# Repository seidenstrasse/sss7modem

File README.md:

SSS7 Modems
===========
SSS7 is the **S**eidenstrasse **S**ignaling **S**ystem 7.

**This is still work in progress, contact me before building hardware !**

This repository contains the schematics its the hardware,
along with a description of the physical layer and the transport layer.
The actual application layer is developed independently of this project.

Physical Layer
--------------
The physical layer is based on a RS485-like two wire bus
(normal RS485 has different levels when idle),
using the *MCP2551* is used as transceiver chip.
Since this chip is actually a CAN-transceiver,
it has a well defined behaviour in case of collisions
and it allows to read back the bits which were actually on the bus while sending.
For regular RS485 transceivers a collision on the bus results
in one transceiver pulling the bus while the other one pulls it high,
effectively creating a temporary short circuit.
Therefore using a CAN-transceiver is preferable for our bus configuration.

The MCP2551 requires that the levels of the differential data lines are within +-7V
of its ground potential.
This a bit of a problem, since it is not really practical to run an additional wire
along the bus to provide a common ground.
Additionally routers may use power supplies which do not have a floating ground potential
(e.g. a computer power supply).
Connecting the ground rails of two non-floating power supplies will lead to a problems.
Therefore an isolated DC/DC converter is used to provide a floating supply voltage
for the transceiver chip and the data lines are isolated using optocouplers.
Still a common ground potential for all nodes is required for the transceiver chips to work.
This is solved by adding diodes in blocking direction between the floating 5v rail and both data lines
and between the chips ground and both data lines.
If the potential of the high data line is more than 0.7v above the floating 5v rail,
on of diodes will become conducting effectively shifting the floating grounds potential up.
Likewise if the potential of the low data line is more than 0.7v below the floating ground rail,
the ground rail will be shifted down.
Hence the floating grounds rails of all modems connected to bus will be within +-0.7v
relative to each other(not considering the voltage drop over the long wires).

Additionally these diodes suppress voltages spikes on the bus,
protecting the transceiver.

Using a sss7modem any device with a decent UART (microcontroller, raspi ...)
can communicate over long distances (1000m+).
The data is send at 9600 Baud (aka. 9,6kbit/s) with a maximum baudrate error of +-5%,
to ensure that even the slowest microcontroller can participate in the communication.
A slow bitrate also necessary to keep communication and collision detection reliable over longer
distances and allows to use slower (and cheaper) optocouplers.

Transport Layer
---------------

### Frame format:
``` 0xAA 0xFE <payload 16 bytes> <payload crc 1byte> ```

19 bytes total

**Header: 0xAA 0xFE**
- Choosen emperically to help the Uarts to synchronize
- Improves detection of two headers colliding

**CRC-Type: Maxim iButton 8-bit**
Polynomial: x^8 + x^5 + x^4 + 1 (0x8C)
Initial value: 0x0

### Communication Protocol

- **Not final, use with caution**
- Frames are sent using standard RS232 Uarts connected to sss7 modems
- Uarts should be configured to: 9600baud, 8bits, 1 stop bit, no flow-control, no parity
- Every node can send a frame at an arbitrary point in time,
    unless it is currently receiving a frame.
- Collision detection on the sender side is done by reading back each sent byte.
- Collision checking on receiver side, is done by checking the CRC and frame header.
- If a frame has been started and there are no new bytes received for 50ms,
    the frame is considered timed out and all received data can be dropped.
- Incoming messages are stored in a fifo until the application retrieves them.
- The receive fifo has a size of at least 2 messages.
- If the fifo is full all new messages will be dropped until messages are retrieved from the fifo.
    It is up to the application to retrieve message in time.
- Even if sending was successful, there is still a chance that the receiver could not
    receive the frame due to missing buffer space or not enough processing time to react.
    **Important messages should utilize a ack-mechanism.**
- It is up to the application to resend messages in case of a collision/missing ack.

### Planned API
- **Not final, use with caution**
- All calls are non-blocking,
    any real work should be done by ISRs or an eventloop, which is called periodically.

- **sss7_can_send()**

    Checks wether we see the bus as idle.
    Return true iff. we neither are currently receiving a frame
    nor are sending a frame of our own.

- **sss7_send_failed()**

    Checks the send error flag.
    Returns true if the last attempt at sending a frame failed.
    An attempt is considered failed if the Uart reads back a different byte than the byte send out.
    This indicates either a collision or a hardware failure.

- **sss7_send(payload)**

    Constructs a frame around the payload and prepares for sending.
    The actual sending is either done in the ISR or by the eventloop, depending on the platform.
    The frame is completely sent iff. ```sss7_can_send() && !sss7_send_failed()``` holds.

- **sss7_has_received()**

    Returns True iff. the receive fifo contains at least one message.

- **sss7_get_received(payload)**

    Retrieves the oldest message from the receive fifo.
    It is up the application to provide sufficient space in payload.
    Does nothing sss7_has_received() is false.

Licenses
--------

Anything in the folder hardware/libs/smisitoto_eu/ is taken from http://smisioto.no-ip.org/elettronica/kicad/kicad-en.htm
The files are made avaible under the Creative Commons license rev2.5 Attribution-ShareAlike. (see https://creativecommons.org/licenses/by-sa/2.5/)

The Chaos InKL logo is licensed CC BY-NC-SA 3.0.

The seidenstrasse logo and my personal logo are not available under an open license.
Therefore you should ask for permission before using the seidenstrasse logo in derived works.
Also please remove my personal logo if I am not involved in your project.

The schematics and pcb layout files in hardware are released under the *CERN Open Hardware License v1.2*.

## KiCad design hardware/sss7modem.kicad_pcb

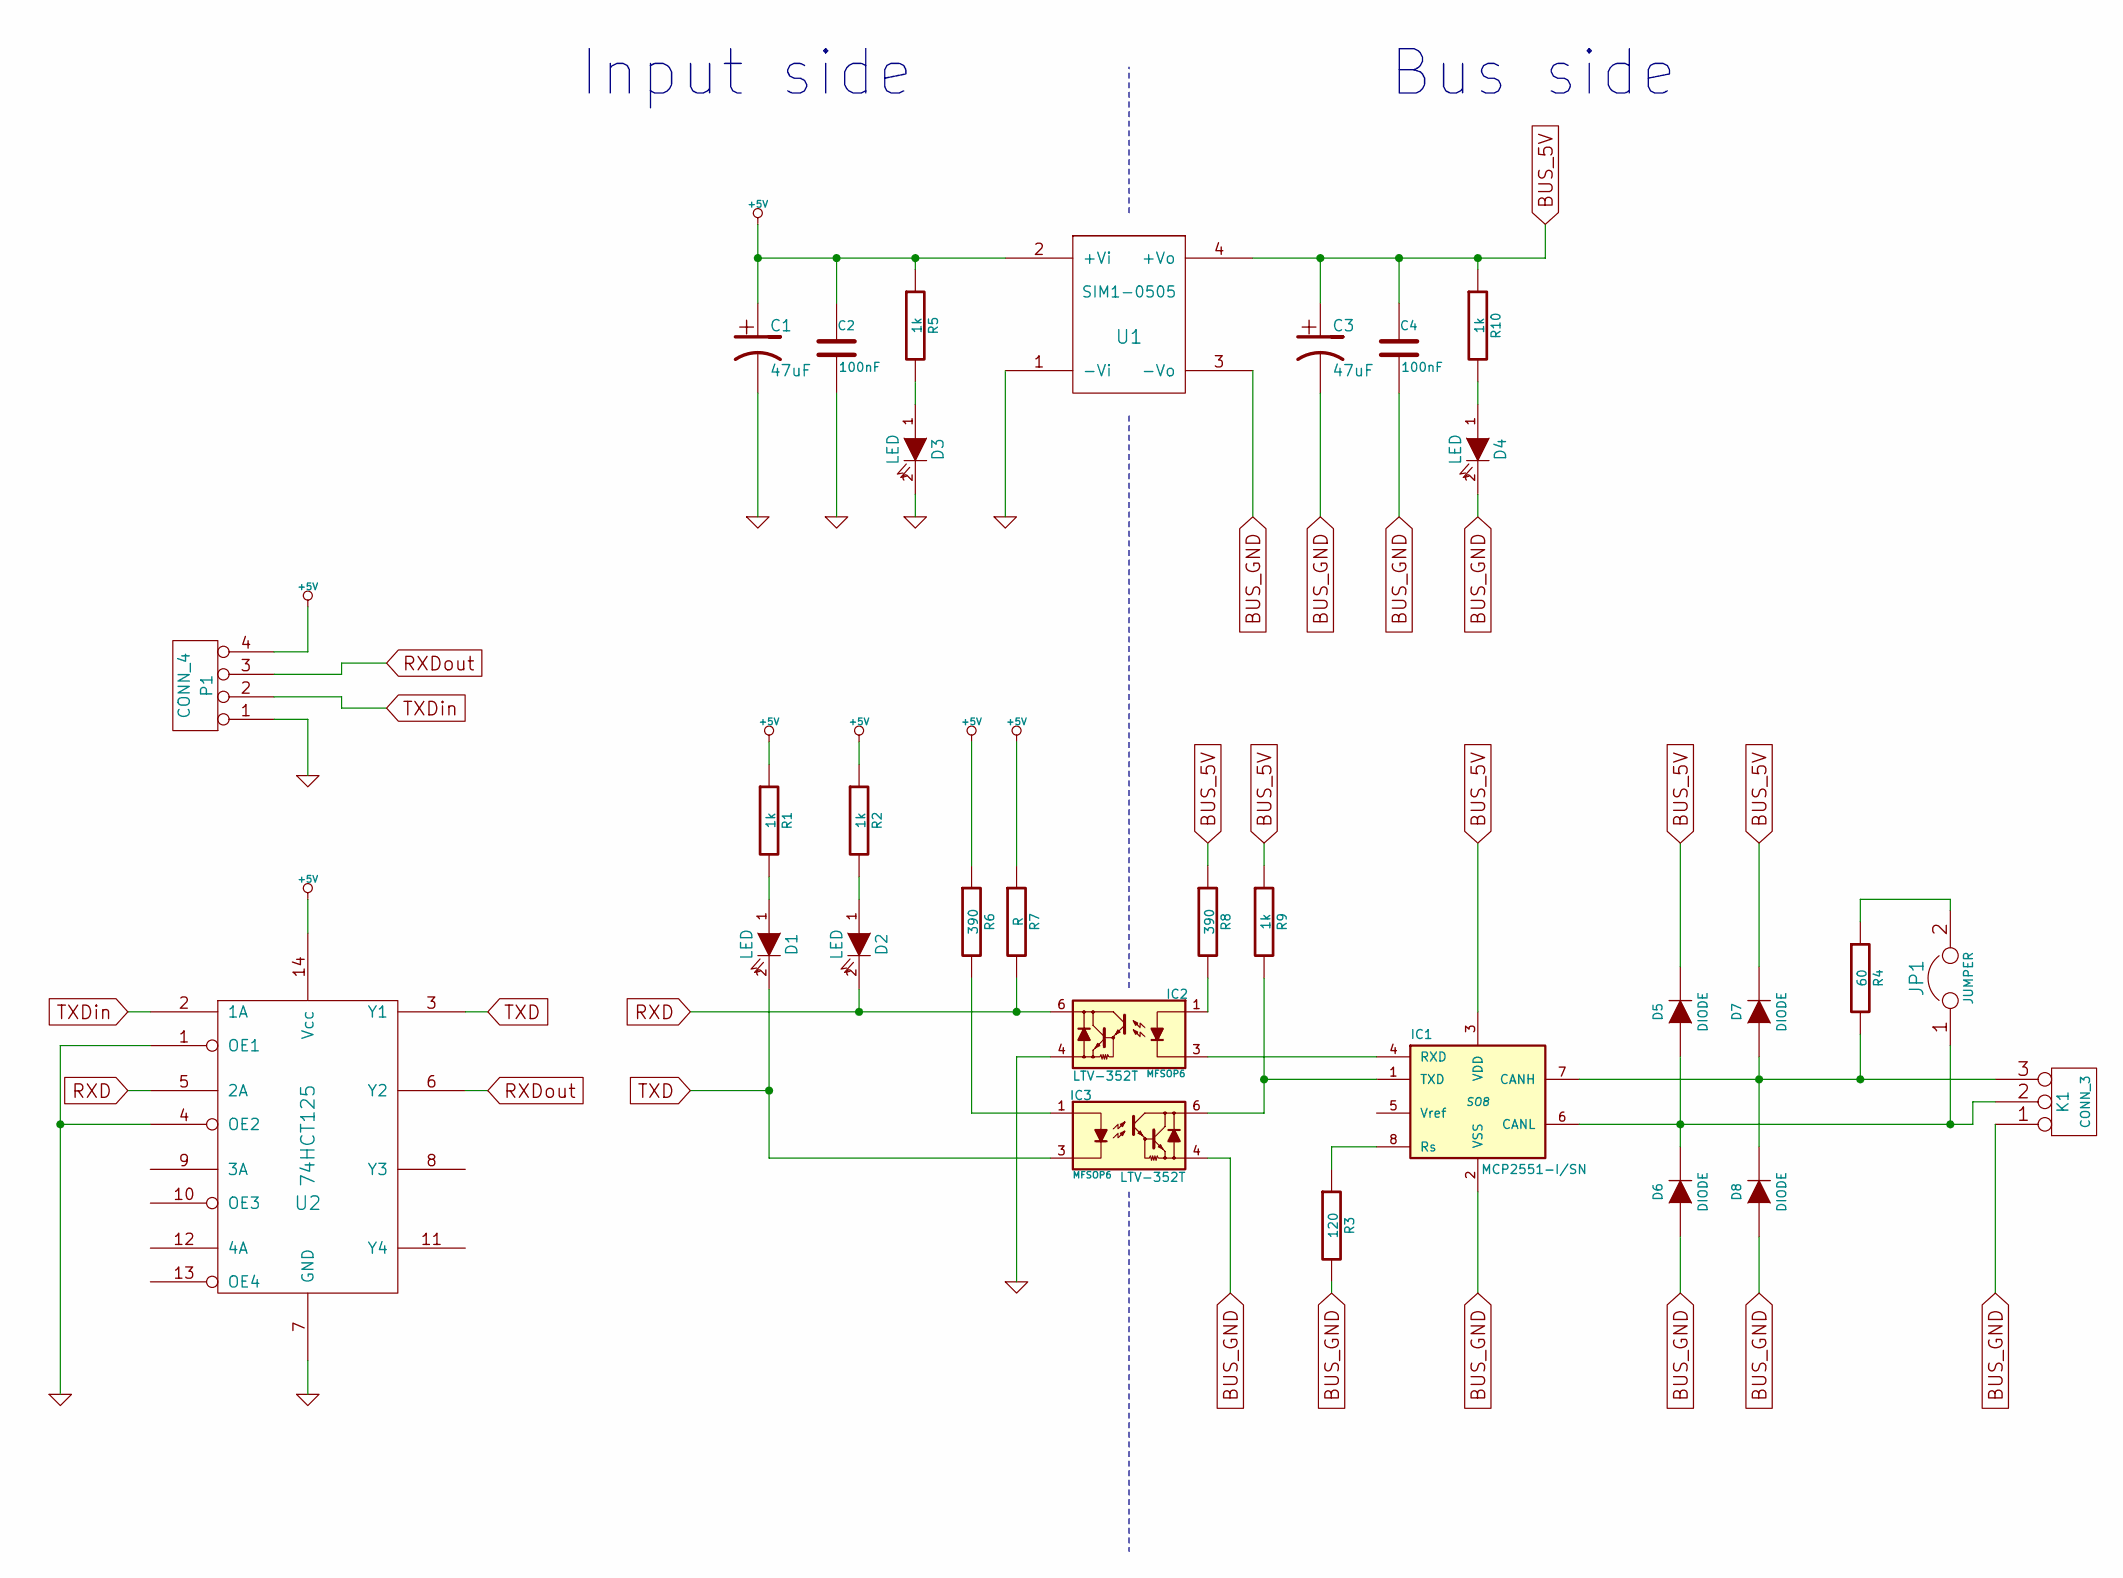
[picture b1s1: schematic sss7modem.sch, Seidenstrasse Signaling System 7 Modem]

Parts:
C1, C3: 47uF
C2, C4: 100nF
D1, D2, D3, D4: LED
D5, D6, D7, D8: DIODE
IC1: MCP2551-I/SN; SO8
IC2, IC3: LTV-352T; MFSOP6
JP1: JUMPER
K1: CONN_3
P1: CONN_4
R1, R2, R5, R9, R10: 1k
R3: 120
R4: 60
R6, R8: 390
R7: R
U1: SIM1-0505
U2: 74HCT125

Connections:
+5V: C1.1, C2.1, P1.4, R1.1, R2.1, R5.1, R6.1, R7.1, U1.2 (+Vi), U2.14 (Vcc)
BUS_5V: C3.1, C4.1, D5.2 (K), D7.2 (K), IC1.3 (VDD), R8.1, R9.1, R10.1, U1.4 (+Vo)
BUS_GND: C3.2, C4.2, D4.2 (K), D6.1 (A), D8.1 (A), IC1.2 (VSS), IC3.4, K1.1, R3.2, U1.3 (-Vo)
GND: C1.2, C2.2, D3.2 (K), IC2.4, P1.1, U1.1 (-Vi), U2.1 (OE1), U2.4 (OE2), U2.7 (GND)
unnamed: IC3.1, R6.2
unnamed: D2.1 (A), R2.2
unnamed: D1.1 (A), R1.2
unnamed: D4.1 (A), R10.2
unnamed: D3.1 (A), R5.2
unnamed: IC1.1 (TXD), IC3.6, R9.2
unnamed: IC1.4 (RXD), IC2.3
unnamed: IC2.1, R8.2
unnamed: JP1.2, R4.1
unnamed: D7.1 (A), D8.2 (K), IC1.7 (CANH), K1.3, R4.2
unnamed: D5.1 (A), D6.2 (K), IC1.6 (CANL), JP1.1, K1.2 (PM)
unnamed: IC1.8 (Rs), R3.1
RXD: D2.2 (K), IC2.6, R7.2, U2.5 (2A)
RXDout: P1.3, U2.6 (Y2)
TXD: D1.2 (K), IC3.3, U2.3 (Y1)
TXDin: P1.2, U2.2 (1A)

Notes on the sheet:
Bus side
Input side

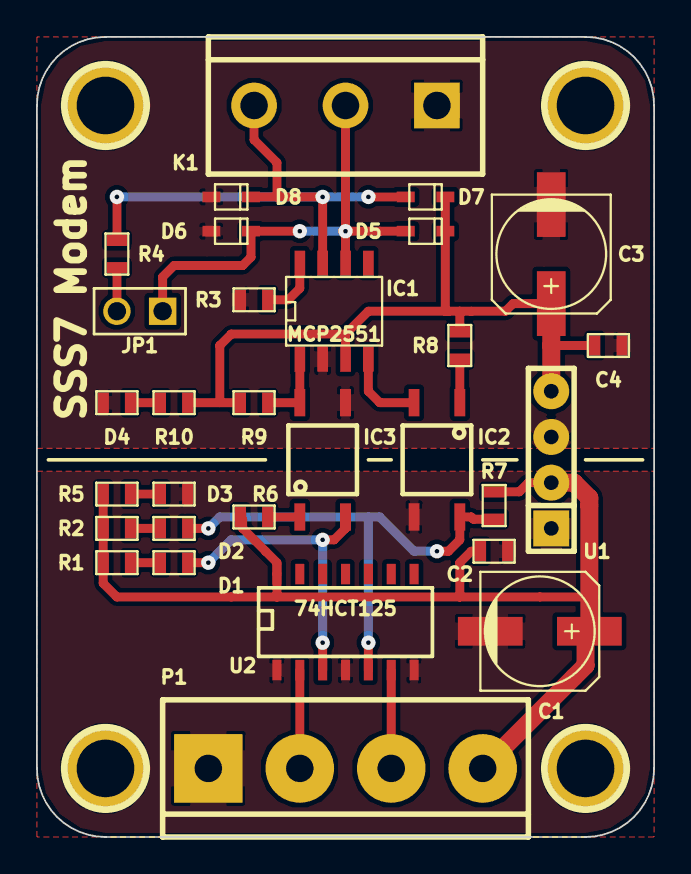
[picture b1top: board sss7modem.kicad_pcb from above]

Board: 2 copper layers, 34.3 x 44.4 mm, 34 parts (0 on the bottom side), 20 nets.

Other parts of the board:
1PIN, 1PIN#2, 1PIN#3, 1PIN#4: P***; 1pin

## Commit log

2015-05-20 Fixed spelling mistakes and defined timeouts
2015-05-20 Fixed typos in RS485 and made stuff clearer
2015-05-21 Changed schematic for floating common on bus side
2015-05-21 Added a pdf so others can take a look as well
2015-05-22 First draft for the split ground pcb
2015-05-25 Made boards smaller for panalizing
2015-05-26 Added logos, started to clean up silkscreen
2015-05-27 Update readme to explain the common ground problem
2015-05-27 Finalized pcb layout and silkscreen
2015-05-27 Generated gerbers
2015-06-02 Added bounding box to workaround bugs in the panelizer tool
2015-06-02 In retrospective this did not make anything better Revert "Added bounding box to workaround bugs in the panelizer tool"
    This reverts commit c11f25827b3cbd9794efebe66123eeaa10cdf22c.
2015-06-26 Added missing resistor value
2015-06-26 First draft for a computer side python implementation
2015-06-26 Cleaned up control flow
2015-06-26 Small fixes
2015-06-28 Added preamble to frames
2015-07-08 Changes optocouplers to something faster. fixes #1
2015-11-06 Fixed resistor values
2016-10-26 Adjusted termination resistor and rebuild gerbers
2016-10-26 Smaller software tweaks
2016-10-26 Documented the new simpler transport layer
2016-10-27 Added parts of the avr library
2016-10-27 Sending parts works Added logic to detect bytes being send but never received
2016-10-28 Fixed tx_failed flag not being reset Fixed makefile
2016-10-28 Added python tool for bus sniffing
2016-10-29 Fixed typo 2 + 16 + 1 = 19 and not 16 ... why did nobody tell me?
2016-10-29 Added crc check to sniffer
2016-10-29 Added test util for sending frames Adjusted timeouts for slow uarts
2016-10-30 Fixed rx buffer behaviour Fixed bytes being swapped in error message
2016-11-20 Fixed sniffer crashing on timeout
2016-11-20 Started to seperate AVR specific code from SSS7 core
2016-11-21 Added Timeouts (untested)
2016-11-21 Seperated core logic from avr8 code
2016-11-21 Uart part of arduino wrapper done
2016-11-21 Added timer code for timeouts
2016-11-21 Enabled timeout timer
2016-11-21 Fixed makefile from spilling object files in the wrong place
2016-11-22 Fixed makefile branding
2016-11-26 Started linux port
2016-11-26 Added a makefile to compile with Arduino libraries Added a extern "C" to sss7.h
2016-11-26 Switched to UART2 as UART1 does not work on my board Tested sending and Timeouts, looks good so far
2016-11-26 Fixed sss7_has_received()
2016-11-26 Fixed sniff.py for fragments
2016-11-26 Fixed timeout timers
2016-11-29 Improved buffer management Buffers should not be overwritten while they could potentially be read
2016-11-30 Added threads and mutexes for eventloop
2016-11-30 Made the sss7core actually use _Atomic
2016-11-30 Implemented timeouts for linux port
2016-12-01 Cleaned up and added teardown
2016-12-02 Started general cleanup and added comments
2016-12-02 Even more comments added
2016-12-03 More cleanup and comments
2016-12-03 Fixed linking
2016-12-03 Started jna port
2016-12-04 Fixed debug output Added better test
2016-12-04 Use Memory instead of abusing Strings
2016-12-19 Staretd work on Python port
2016-12-19 SSS7 should be a signleton
2016-12-19 Added synchronized to become thread-safe Added README
2016-12-19 Fixed SSS7 class trying to use the empty string as serialport Should have had a coffee first.
2016-12-20 added c99
2016-12-20 added real stuff maybe wrong place to commit (sorry)
2016-12-22 Reverted because it fucks up all the automated tests This reverts commit d3b003b9763968688bea41bd781e62ef5b4e4e78.
2016-12-22 Totally the wrong place Revert "added real stuff maybe wrong place to commit (sorry)"
    This reverts commit ba4616e152fde6ce86b764eb18ae483fef601afb.
2016-12-22 Fixed sending part
2016-12-22 Added SSS7_TX_FINALIZE state Fixes #2
2016-12-23 Python should work now
2016-12-25 Untested Arduino code for mega328
2016-12-25 Using the right interrupts should help
2016-12-26 Fixed various things
2016-12-26 Fixed testutils
2016-12-28 Added simple bus testing code
2017-12-27 Added some fixes for c++ compatebility
